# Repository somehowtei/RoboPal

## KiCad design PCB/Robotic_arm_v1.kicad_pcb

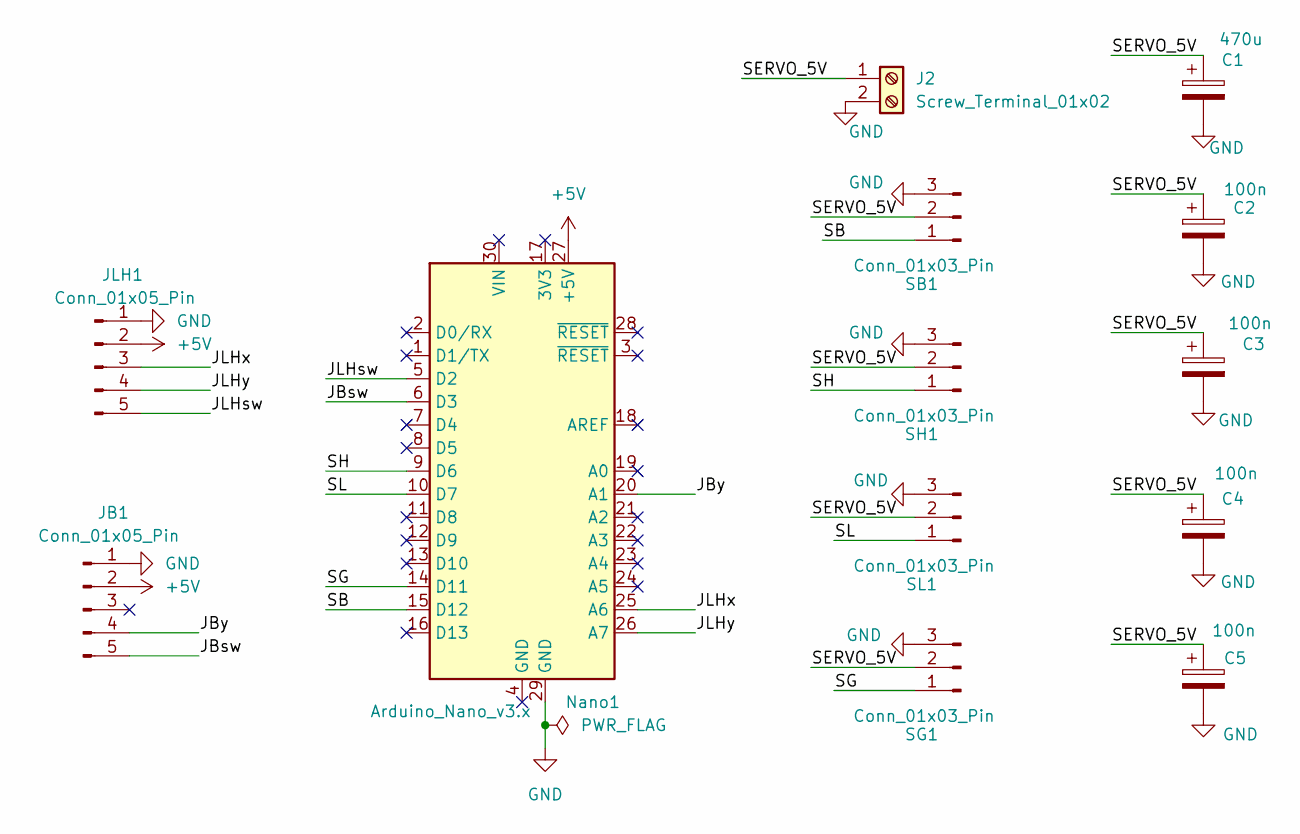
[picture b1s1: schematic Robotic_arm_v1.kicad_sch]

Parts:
C1: 470u; CP_Radial_D8.0mm_P5.00mm
C2, C3, C4, C5: 100n; C_Disc_D5.0mm_W2.5mm_P2.50mm
J2: Screw_Terminal_01x02; TerminalBlock_Phoenix_MKDS-1,5-2-5.08_1x02_P5.08mm_Horizont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
JB1: Conn_01x05_Pin; joystick
JLH1: Conn_01x05_Pin; joystick
Nano1: Arduino_Nano_v3.x; Arduino_Nano
SB1: Conn_01x03_Pin; PinHeader_1x03_P2.54mm_Vertical
SG1: Conn_01x03_Pin; PinHeader_1x03_P2.54mm_Vertical
SH1: Conn_01x03_Pin; PinHeader_1x03_P2.54mm_Vertical
SL1: Conn_01x03_Pin; PinHeader_1x03_P2.54mm_Vertical

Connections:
+5V: JB1.2, JLH1.2, Nano1.27 (+5V)
/JBsw: JB1.5, Nano1.6 (D3)
/JBy: JB1.4, Nano1.20 (A1)
/JLHsw: JLH1.5, Nano1.5 (D2)
/JLHx: JLH1.3, Nano1.25 (A6)
/JLHy: JLH1.4, Nano1.26 (A7)
/SB: Nano1.15 (D12), SB1.1
/SERVO_5V: C1.1, C2.1, C3.1, C4.1, C5.1, J2.1, SB1.2, SG1.2, SH1.2, SL1.2
/SG: Nano1.14 (D11), SG1.1
/SH: Nano1.9 (D6), SH1.1
/SL: Nano1.10 (D7), SL1.1
GND: C1.2, C2.2, C3.2, C4.2, C5.2, J2.2, JB1.1, JLH1.1, Nano1.29 (GND), SB1.3, SG1.3, SH1.3, SL1.3

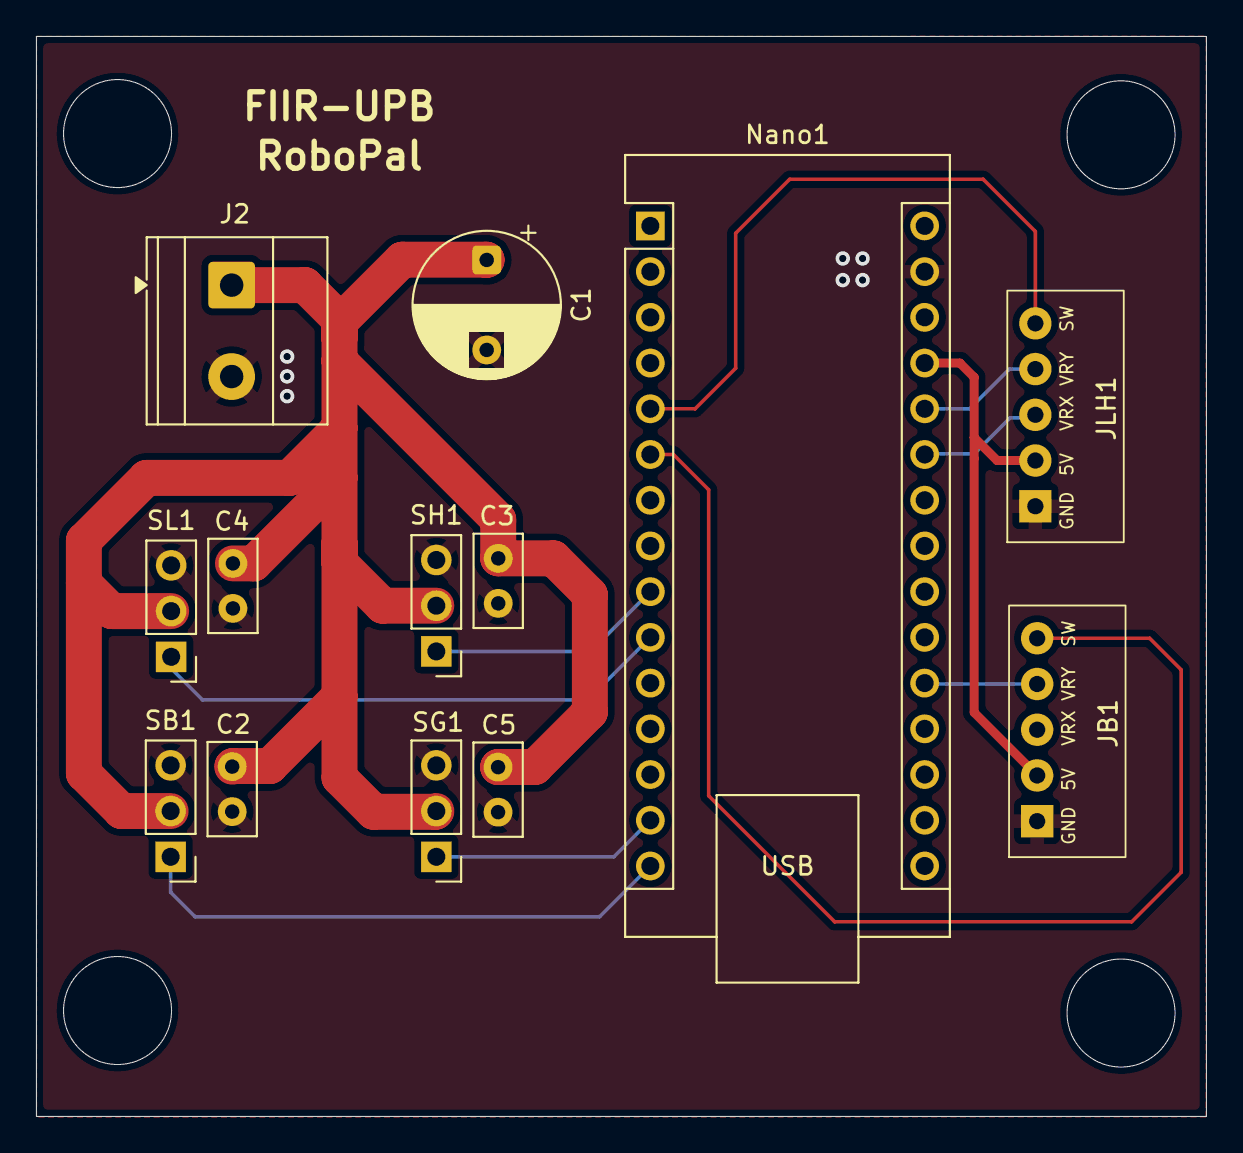
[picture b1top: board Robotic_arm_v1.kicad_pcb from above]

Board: 2 copper layers, 65.0 x 60.0 mm, 13 parts (0 on the bottom side), 12 nets.
